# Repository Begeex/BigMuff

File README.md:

# BigMuff

This project is a clone of the Electro-Hrmonix Big Muff guitar pedal. This version uses 2N5089 transistors and 1N4148 diodes.

### Circuit

The pedal is based on a circuit diagram by ElectroSmash. The schematic and parts list are available from the link below.
https://www.electrosmash.com/big-muff-pi-analysis

### PCB

The PCB was designed using KiCad software and can be seen below as a 3D render. It's designed to fit in a 1590B enclosure and is 55 mm x 71 mm in size. Through hole components were selected for easier assembly at home.

The KiCad and Gerber files are available in this repository.

### Ready PCB

### Assembled PCB

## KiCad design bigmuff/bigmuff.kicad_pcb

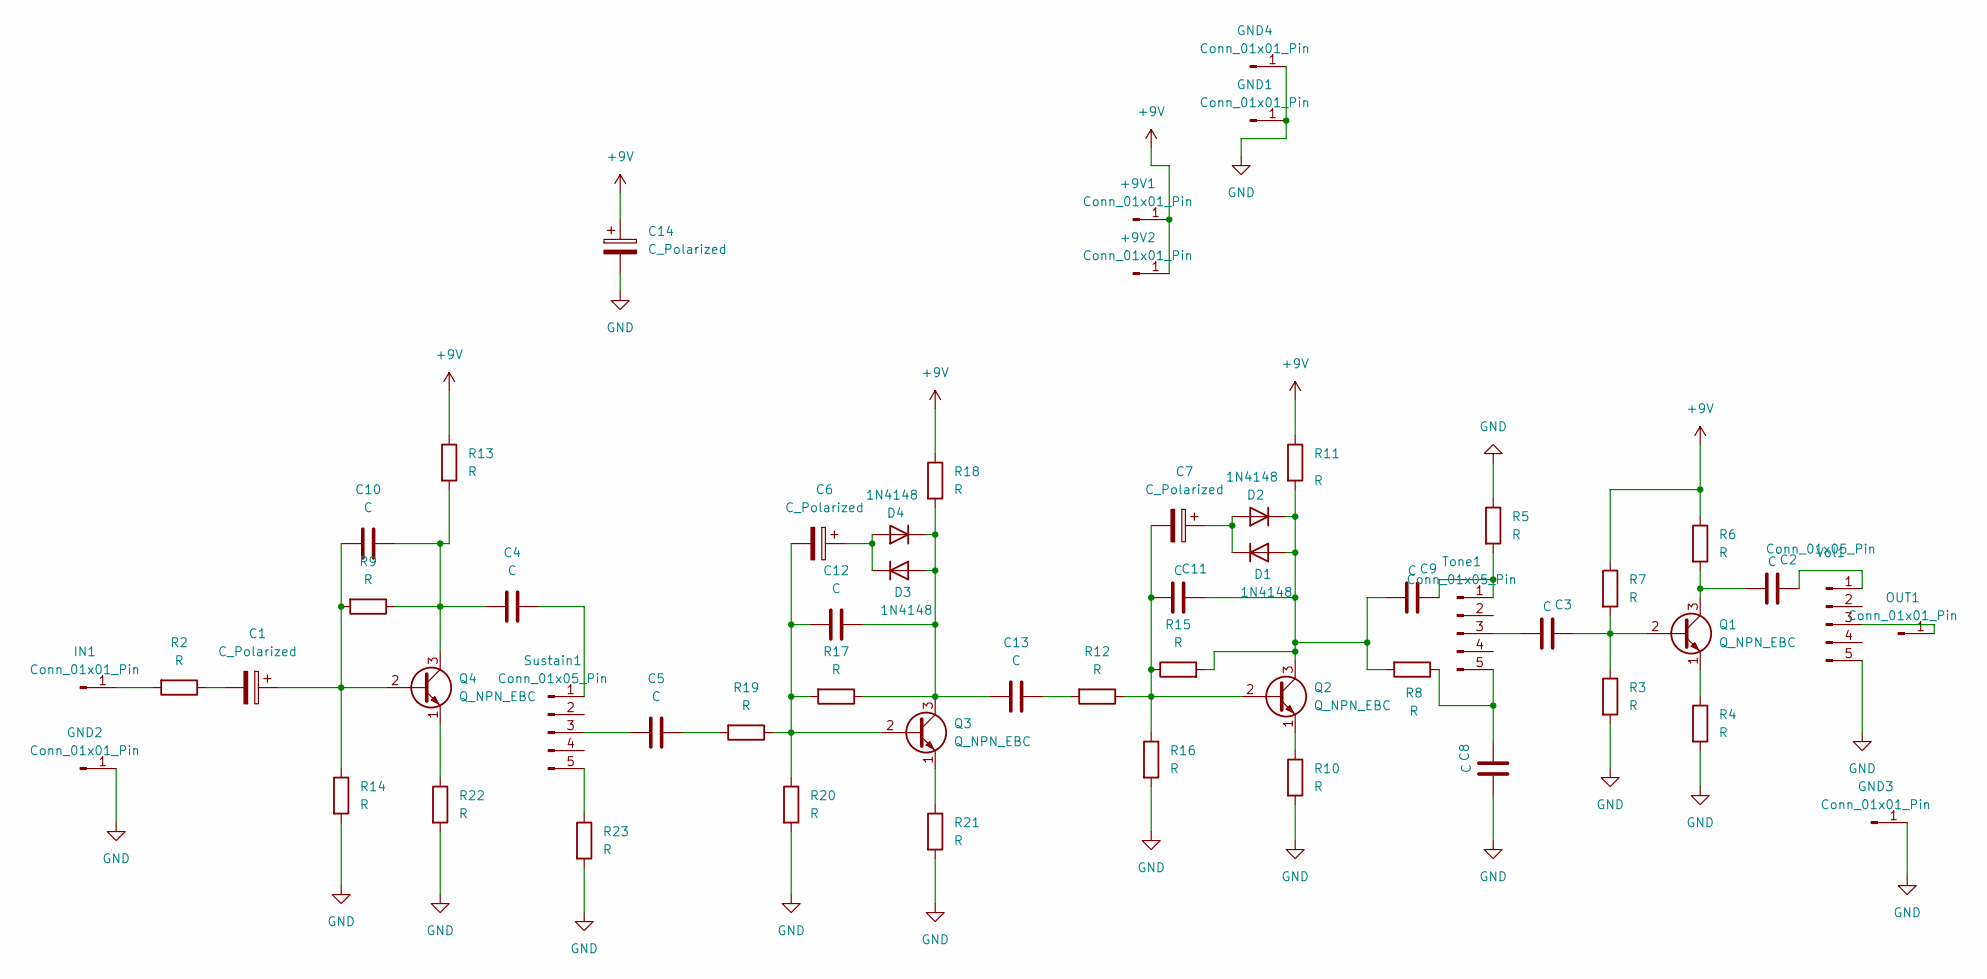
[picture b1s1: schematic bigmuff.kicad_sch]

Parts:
+9V1, +9V2: Conn_01x01_Pin; PinHeader_1x01_P2.54mm_Vertical
C1, C6, C7, C14: C_Polarized; CP_Radial_D6.3mm_P2.50mm
C2, C3, C4, C5, C8, C9, C10, C11, C12, C13: C; C_Rect_L7.0mm_W2.0mm_P5.00mm
D1, D2, D3, D4: 1N4148; D_DO-35_SOD27_P7.62mm_Horizontal
GND1, GND2, GND3, GND4: Conn_01x01_Pin; PinHeader_1x01_P2.54mm_Vertical
IN1: Conn_01x01_Pin; PinHeader_1x01_P2.54mm_Vertical
OUT1: Conn_01x01_Pin; PinHeader_1x01_P2.54mm_Vertical
Q1, Q2, Q3, Q4: Q_NPN_EBC; TO-92
R2, R3, R4, R5, R6, R7, R8, R9, R10, R11, R12, R13, R14, R15, R16, R17, R18, R19, R20, R21, R22, R23: R; R_Axial_DIN0207_L6.3mm_D2.5mm_P7.62mm_Horizontal
Sustain1: Conn_01x05_Pin; PinHeader_1x05_P2.54mm_Vertical
Tone1: Conn_01x05_Pin; PinHeader_1x05_P2.54mm_Vertical
Vol1: Conn_01x05_Pin; PinHeader_1x05_P2.54mm_Vertical

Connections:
+9V: +9V1.1, +9V2.1, C14.1, R6.1, R7.1, R11.1, R13.1, R18.1
GND: C8.2, C14.2, GND1.1, GND2.1, GND3.1, GND4.1, R3.2, R4.2, R5.1, R10.2, R14.2, R16.2, R20.2, R21.2, R22.2, R23.2, Vol1.5
unnamed: C1.2, R2.1
unnamed: C5.1, R19.2
unnamed: C13.1, R12.2
unnamed: C9.2, C11.1, D1.2 (A), D2.1 (K), Q2.3 (C), R8.2, R11.2, R15.2
unnamed: C7.1, D1.1 (K), D2.2 (A)
unnamed: C12.1, C13.2, D3.2 (A), D4.1 (K), Q3.3 (C), R17.1, R18.2
unnamed: C6.1, D3.1 (K), D4.2 (A)
unnamed: IN1.1, R2.2
unnamed: OUT1.1, Vol1.3
unnamed: C3.1, Q1.2 (B), R3.1, R7.2
unnamed: C2.2, Q1.3 (C), R6.2
unnamed: Q1.1 (E), R4.1
unnamed: C7.2, C11.2, Q2.2 (B), R12.1, R15.1, R16.1
unnamed: Q2.1 (E), R10.1
unnamed: C6.2, C12.2, Q3.2 (B), R17.2, R19.1, R20.1
unnamed: Q3.1 (E), R21.1
unnamed: C1.1, C10.2, Q4.2 (B), R9.2, R14.1
unnamed: C4.2, C10.1, Q4.3 (C), R9.1, R13.2
unnamed: Q4.1 (E), R22.1
unnamed: C4.1, Sustain1.1
unnamed: C5.2, Sustain1.3
unnamed: R23.1, Sustain1.5
unnamed: C9.1, R5.2, Tone1.1
unnamed: C3.2, Tone1.3
unnamed: C8.1, R8.1, Tone1.5
unnamed: C2.1, Vol1.1

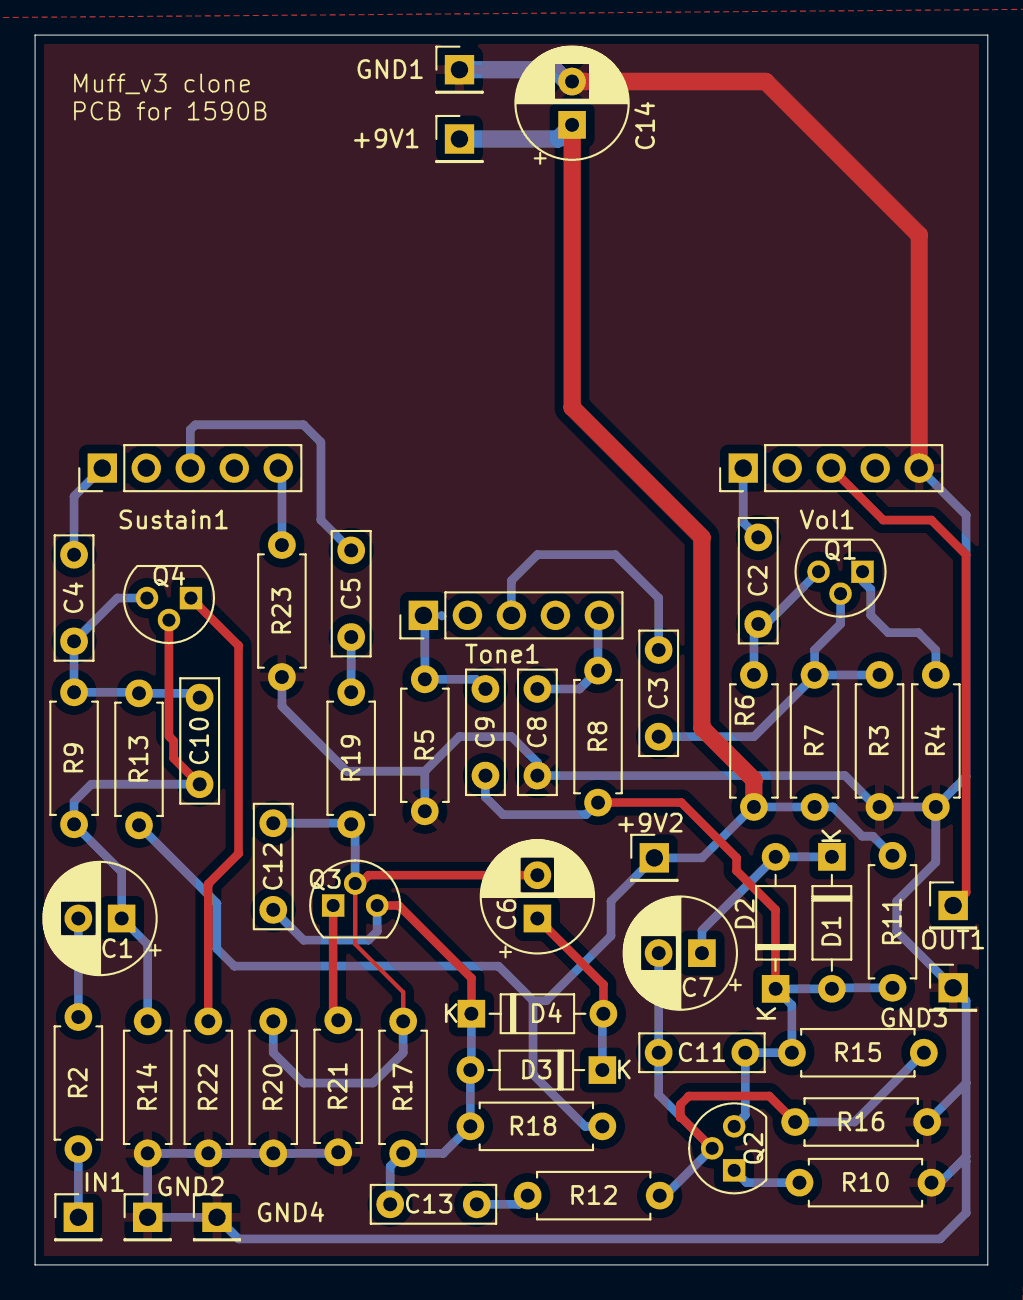
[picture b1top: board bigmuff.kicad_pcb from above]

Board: 2 copper layers, 55.0 x 71.0 mm, 55 parts (0 on the bottom side), 28 nets.

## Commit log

2026-01-21 Added pictures
2026-01-21 Added KiCad files
2026-01-21 Added Gerber and drill files
    Gerber and drill files for manufacturing of the PCB
